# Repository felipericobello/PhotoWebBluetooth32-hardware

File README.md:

# PhotoWebBluetooth (Hardware)

Este repositório contém todos os arquivos de hardware, esquemas eletrônicos e modelos 3D para a construção do sistema **PhotoWebBluetooth32 (PWB32)**.

O PWB32 é um sistema photogate de seis canais de baixo custo, desenvolvido para laboratórios de ensino de Física. Ele utiliza um microcontrolador ESP32 para detectar a passagem de objetos por sensores infravermelhos e transmite os dados via Bluetooth para uma interface web.

> **Nota:** Este hardware foi desenvolvido como parte do Trabalho de Conclusão de Curso de **Felipe Ricobello**, com colaboração técnica de **Aline de Almeida Soares** e **Fernando Rezende Apolinário** (CCA/UFSCar). Para o código-fonte do firmware e da interface web, acesse o repositório [PhotoWebBluetooth32](https://github.com/jocoteles/PhotoWebBluetooth32).

---

## 🛠 Conteúdo do Repositório

Este repositório está organizado nas seguintes pastas:

*   **`/PCB`**: Contém os esquemas do circuito, layout da PCB (se aplicável) e a lista de componentes (BOM) detalhada.
*   **`/STL`**: Inclui os arquivos STL e, possivelmente, os arquivos de projeto (ex: Fusion 360, OpenSCAD) para os cabeçotes dos sensores photogate e a caixa de acondicionamento do ESP32.
*   **`/DOCS`**: Apresenta diagramas de montagem, fotos do sistema finalizado e qualquer outra documentação relevante para a construção.

---

## 📋 Lista de Materiais (BOM - Bill of Materials)

Para montar uma unidade completa de 6 canais do PhotoWebBluetooth32, você precisará dos seguintes componentes:

### Eletrônica Principal
*   1x **ESP32 DevKit V1** (com 30 pinos, ou modelo compatível).
*   6x **Pares Infravermelhos** (compostos por 1x LED IR emissor e 1x Fototransistor receptor cada).
*   6x **Resistores para os LEDs IR** (valor típico: 150Ω a 220Ω, dimensionado conforme a corrente desejada e tensão de alimentação do LED).
*   6x **Resistores de pull-up para os fototransistores** (valor típico: 10kΩ).
*   **Cabos de conexão:** Fios para ligar os sensores ao ESP32 (recomenda-se cabos blindados ou do tipo flat para os sensores para maior organização e menos ruído).
*   **Conectores (opcional):** Conectores de 3 pinos (ex: JST, GX16) para os sensores para facilitar a modularidade e substituição.
*   **Protoboard ou PCB:** Para a montagem do circuito de condicionamento de sinal e conexão dos sensores.

### Estrutura (Impressão 3D)
*   6x **Corpos de cabeçotes de sensores** (design em "U" disponível em `/modelagem-3d`, para garantir o alinhamento do feixe IR).
*   1x **Caixa de controle** (disponível em `/modelagem-33`, para abrigar o ESP32 e as conexões principais).
*   **Parafusos e porcas** para fixação (detalhes no manual de montagem).

---

## 🔌 Pinagem e Circuito

O firmware padrão do PhotoWebBluetooth32 espera que os sensores photogate sejam conectados aos seguintes pinos analógicos do ESP32:

| Canal | Pino ESP32 (ADC) | Função |
| :--- | :--- | :--- | :--- |
| Canal 1 | GPIO 34 | Sensor Photogate 1 |
| Canal 2 | GPIO 35 | Sensor Photogate 2 |
| Canal 3 | GPIO 32 | Sensor Photogate 3 |
| Canal 4 | GPIO 33 | Sensor Photogate 4 | 
| Canal 5 | GPIO 25 | Sensor Photogate 5 | 
| Canal 6 | GPIO 26 | Sensor Photogate 6 |

**Diagrama Básico do Sensor Photogate:**

Cada sensor photogate consiste em um LED infravermelho e um fototransistor. O fototransistor é conectado em uma configuração de divisor de tensão, onde sua resistência varia drasticamente com a incidência de luz IR.

Quando um objeto passa e bloqueia o feixe IR, o fototransistor para de conduzir, e a tensão no pino ADC sobe (ou desce, dependendo da configuração). O firmware detecta essa mudança para registrar o evento.

Para o esquema detalhado e layout da PCB, consulte a pasta `/PCB`.

---

## 📐 Montagem Física

1.  **Impressão 3D:** Imprima todas as peças estruturais (`cabeçotes`, `caixa_controle`) utilizando os arquivos STL fornecidos em `/STL`. Recomenda-se PETG ou ABS para durabilidade.
2.  **Montagem da Eletrônica:**
    *   Soldar os resistores e o fototransistor para cada cabeçote de sensor.
    *   Montar o circuito de condicionamento de sinal (se houver) em uma protoboard ou PCB.
    *   Conectar os fios dos 6 sensores aos pinos do ESP32 conforme a tabela de pinagem acima.
    *   Garantir boas conexões de alimentação (3.3V e GND) para o ESP32 e os sensores.
3.  **Acondicionamento:**
    *   Encaixe o ESP32 dentro da caixa de controle impressa.
    *   Passe os cabos dos sensores pelas aberturas da caixa e conecte-os de forma organizada.
    *   Certifique-se de que a antena Wi-Fi/Bluetooth do ESP32 não esteja obstruída por componentes metálicos para garantir a melhor conectividade.
4.  **Montagem dos Cabeçotes:** Insira o LED IR e o fototransistor em seus respectivos orifícios nos cabeçotes impressos. O design em "U" deve facilitar o alinhamento.
5.  **Verificação:** Antes de fechar a caixa, faça uma verificação visual de todas as conexões e soldas.

Para um guia de montagem passo a passo com fotos, consulte a pasta `/documentacao`.

---

## 🚀 Como Integrar com o Software

Após a montagem do hardware:

1.  **Grave o Firmware:** Siga as instruções no repositório [PhotoWebBluetooth32](https://github.com/jocoteles/PhotoWebBluetooth32) para compilar e gravar o firmware `PWB32Server.ino` no seu ESP32.
2.  **Teste com a PWA:** Acesse a Progressive Web App (PWA) em [https://jocoteles.github.io/PhotoWebBluetooth32/](https://jocoteles.github.io/PhotoWebBluetooth32/) com um navegador compatível (Chrome, Edge, Opera em desktop ou Android).
3.  **Calibração:** Utilize a aba "Config" da PWA para ajustar os níveis de trigger de cada canal do photogate conforme as condições de luz do ambiente e a opacidade dos objetos a serem detectados.

---

## 📄 Licença

Este projeto de hardware é liberado sob uma licença de hardware aberto (ex: CERN OHL-P ou Creative Commons Attribution-ShareAlike 4.0 International). Sinta-se à vontade para modificar e melhorar os designs, desde que cite os autores originais.

---
*Desenvolvido para os Laboratórios de Ensino de Física do [CCA/UFSCar](https://www.fisicaararas.ufscar.br/pt-br).*

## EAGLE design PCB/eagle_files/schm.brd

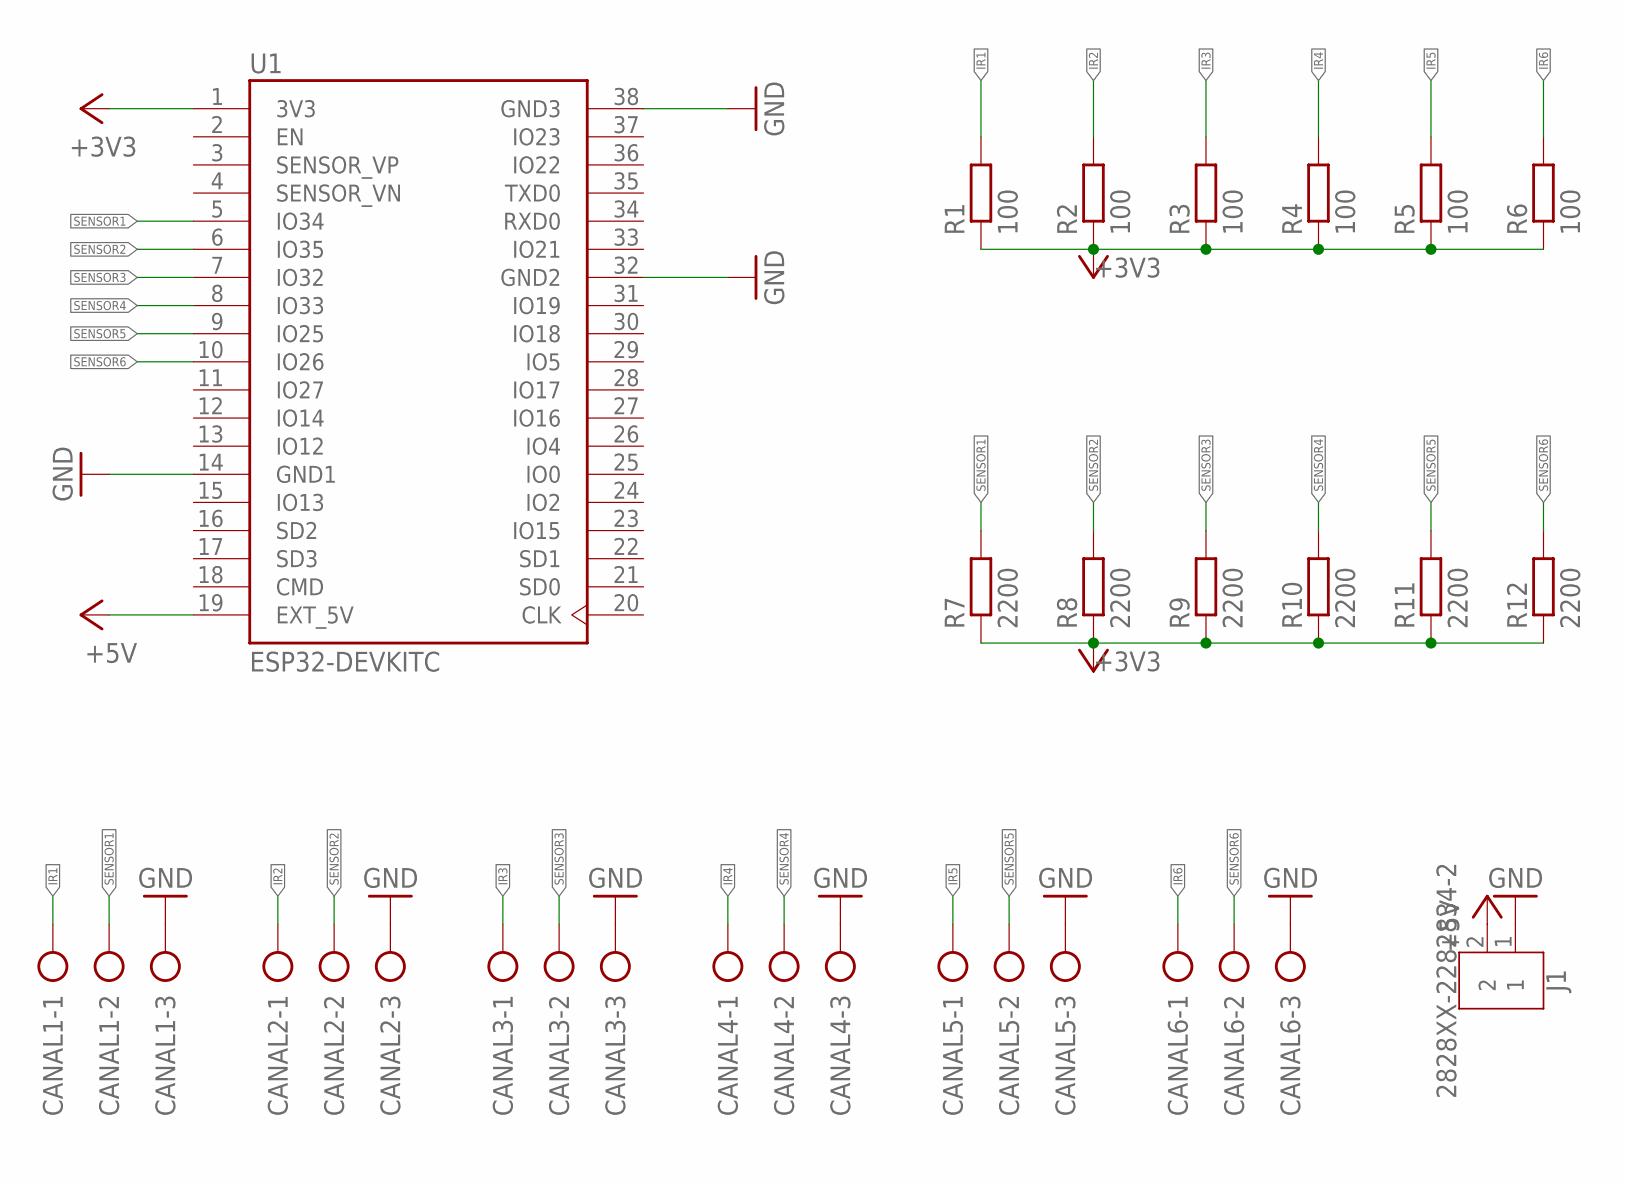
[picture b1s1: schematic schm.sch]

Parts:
CANAL1, CANAL2, CANAL3, CANAL4, CANAL5, CANAL6: AK300/3
J1: 2828XX-2282834-2; TERMBLK_254-2N
R1, R2, R3, R4, R5, R6: 100; 0207/10
R7, R8, R9, R10, R11, R12: 2200; 0207/10
U1: ESP32-DEVKITC; MODULE_ESP32-DEVKITC

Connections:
+3V3: R1.1, R2.1, R3.1, R4.1, R5.1, R6.1, R7.1, R8.1, R9.1, R10.1, R11.1, R12.1, U1.1 (3V3)
+5V: J1.2, U1.19 (EXT_5V)
GND: CANAL1.3, CANAL2.3, CANAL3.3, CANAL4.3, CANAL5.3, CANAL6.3, J1.1, U1.14 (GND1), U1.32 (GND2), U1.38 (GND3)
IR1: CANAL1.1, R1.2
IR2: CANAL2.1, R2.2
IR3: CANAL3.1, R3.2
IR4: CANAL4.1, R4.2
IR5: CANAL5.1, R5.2
IR6: CANAL6.1, R6.2
SENSOR1: CANAL1.2, R7.2, U1.5 (IO34)
SENSOR2: CANAL2.2, R8.2, U1.6 (IO35)
SENSOR3: CANAL3.2, R9.2, U1.7 (IO32)
SENSOR4: CANAL4.2, R10.2, U1.8 (IO33)
SENSOR5: CANAL5.2, R11.2, U1.9 (IO25)
SENSOR6: CANAL6.2, R12.2, U1.10 (IO26)

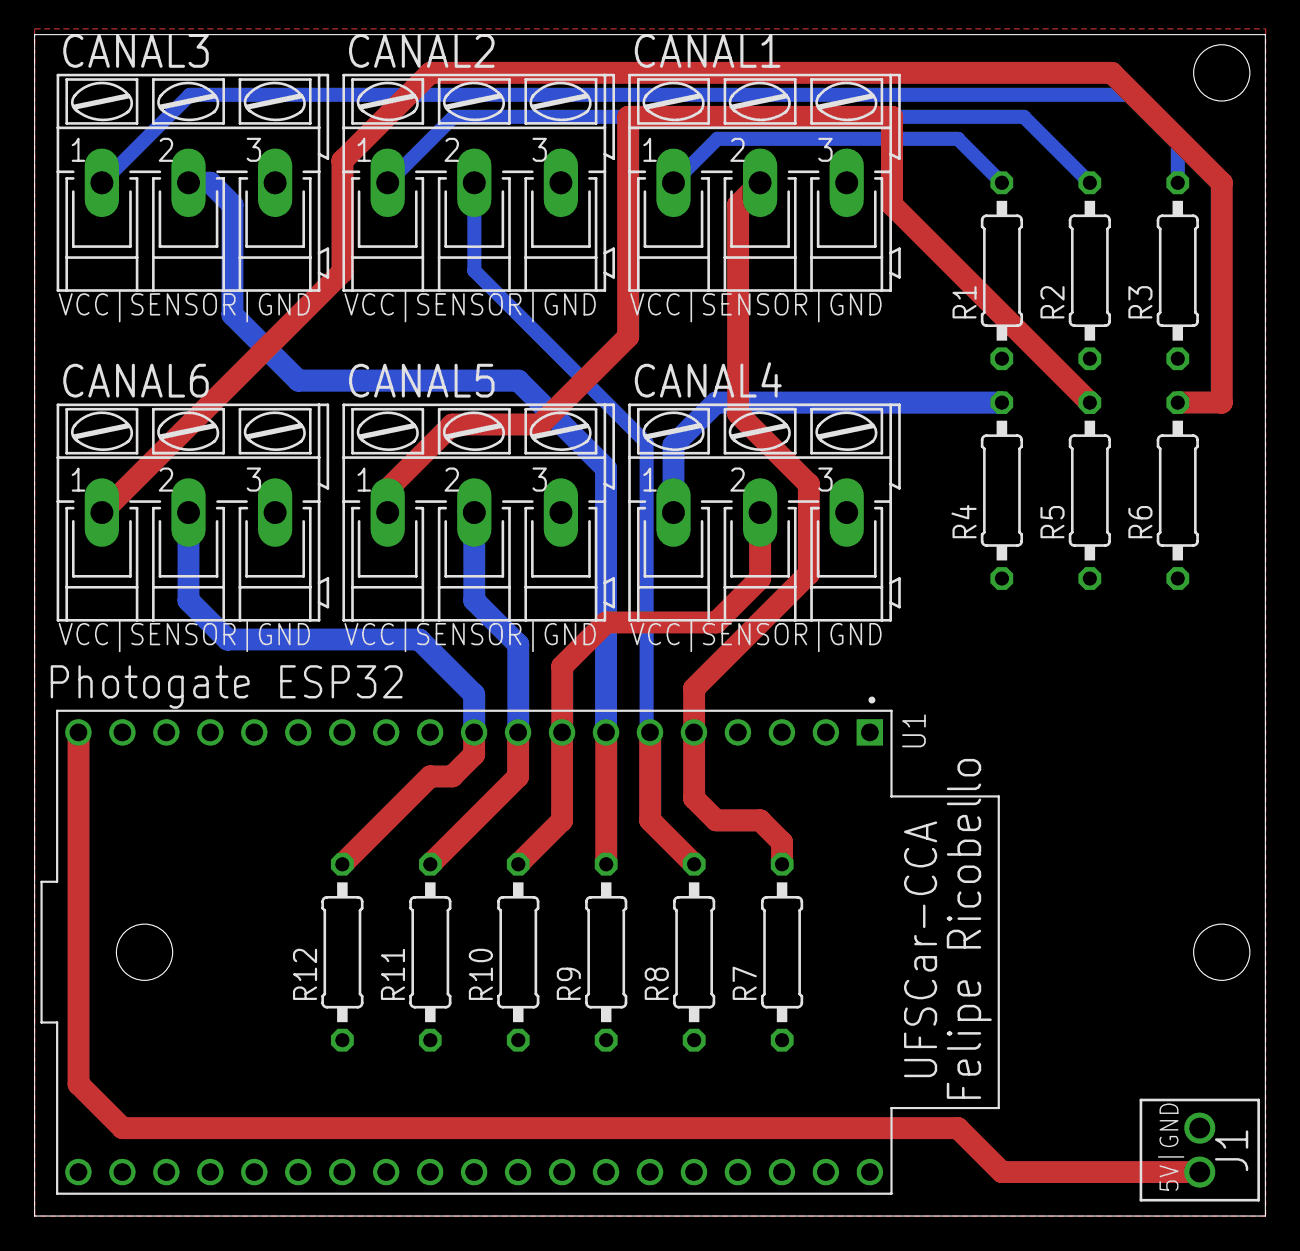
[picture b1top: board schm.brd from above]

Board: 2 copper layers, 71.1 x 68.2 mm, 20 parts (0 on the bottom side), 15 nets.

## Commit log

2025-01-22 WorkingTest
2025-02-24 Rise and fall timestamps working!!!
2025-03-03 OLED implementated
2025-04-28 Photogate speed test
2025-05-05 ESP32WebSocketControl created
2025-05-05 Tiny correction in ArRequestHandlerFunction
2025-05-07 Improvements
2025-05-09 Automatic variables reading and better comments
2025-05-09 ESP32WebSocketControl strongly modularized
2025-05-09 Mudancas pcb
2025-09-29 PWA implementation with Github pages hosting
2026-02-27 Atualizacao Hardware
2026-02-27 README update
